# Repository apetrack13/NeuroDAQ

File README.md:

# NeuroDAQ
<p> The NeuroDAQ is a quality control device for transcranial electrical stimulation (tES) generation devices.
The aim is to improve the outcomes of tES studies by verifying the fidelity of stimulation generation from
tES devices. </p>
<h2>Setting Up the NeuroDAQ</h2>
<p> The NeuroDAQ requires a connection to a local network. </p>

<h3>Setup Wireless Connection</h3>

1.)	Check if micro USB power cable is connected to NeuroDAQ located on the side.

2.)	Remove micro SD card from NeuroDAQ located on the side. 

3.)	Insert micro SD card into adaptor SD card adaptor provided with kit.

4.)	Plug the SD Card adaptor into computer. A new volume should appear in your finder/ file explorer.

5.)	Open the new volume and navigate to the boot directory /Volumes/boot.

6.)	Create a file called wpa_supplicant.conf in this directory and save it.

7.)	Open the file and add the following details:                                                					network={												ssid=”YOUR_NETWORK_NAME”									psk=”YOUR_PASSWORD”									key_mgmt=WPA-PSK

8.)	Eject the SD card and plug it back into the NeuroDAQ.

<h2>Using the NeuroDAQ via Terminal</h2>
<h3>Establish SSH Connection to NeuroDAQ</h3>
<p>
The NeuroDAQ can be controlled via a ssh connection. Once a ssh connection is established, data acquisition can be iniated.
</p>
1.)	First, be sure the micro USB power cable is connected to the NeuroDAQ.

2.)	Open terminal in the applications folder of Mac OS computer.

3.)	Type ssh pi@NeuroDAQ.local and press enter.

4.)	If prompted to answer a yes or no question, type yes and press enter. If not, skip to step 4.

5.)	You will be prompted to enter a password to connect to the device. The password is “GIZMO629” (obviously no quotes).

6.)	You are now connected to the device’s terminal from which you can execute scripts.

<h3>Retrieve Data File</h3>
1.)	In the Mac OS terminal connected to the device, type and enter:					scp pi@NeuroDAQ.local:~/Desktop/DATA_FILE_NAME.csv ~/Desktop		

Replace DATA_FILE_NAME with what you named the data file during data acquisition. 

2.)	The data file will be transferred to the desktop of your Mac OS computer. You now can process this data file with the MATLAB script provided.

<h3>Process Data File with MATLAB</h3>
1.)	Locate the MATLAB script file named “Process_Signal.m”. This script is available at github.com/NeuroModQC-WSU-Design/NeuroDAQ/.

2.)	Place the data file in the same directory as this script.

3.)	Open the script with MATLAB and run.

4.)	You will be prompted to answer questions about the stimulation paradigm recorded. Please, refer to the stimulation paradigm parameters used to record the data file.

5.)	Statistical analysis and graphs of stimulation paradigm will be presented.

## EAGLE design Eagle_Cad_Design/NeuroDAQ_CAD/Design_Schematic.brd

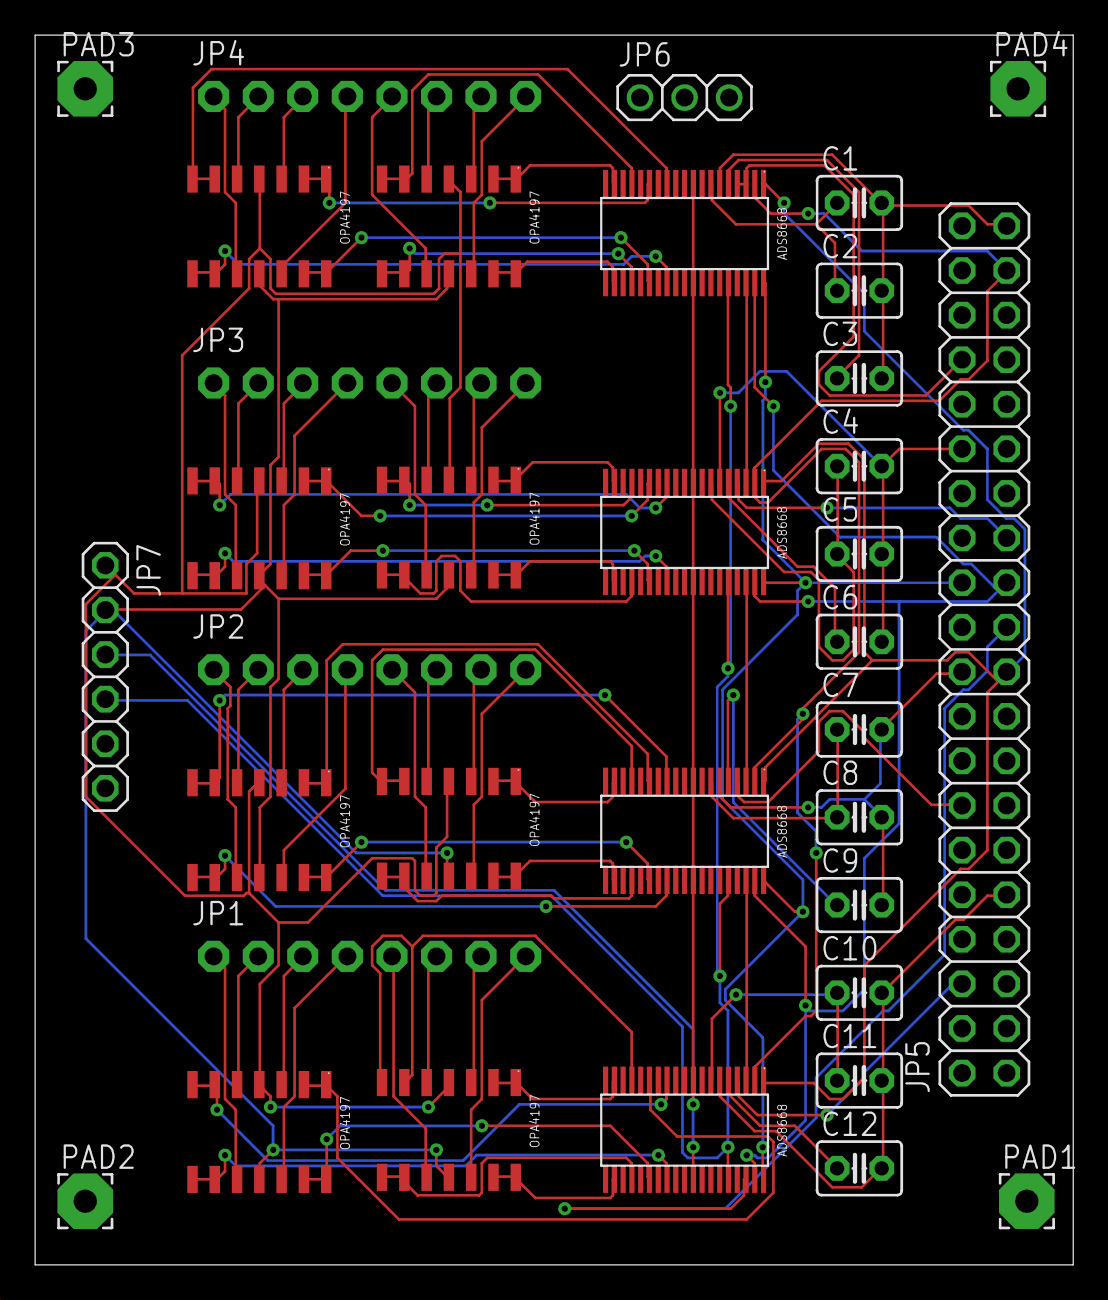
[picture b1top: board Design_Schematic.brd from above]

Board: 2 copper layers, 59.1 x 70.1 mm, 35 parts (0 on the bottom side), 93 nets.

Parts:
ADC1, ADC2, ADC3, ADC4: ADS8668
C1, C2, C3, C4, C5, C6, C7, C8, C9, C10, C11, C12: C025-030X050
JP1, JP2, JP3, JP4: 1X08-CLEANBIG
JP5: 2X20
JP6: 1X03
JP7: 1X06
PAD1, PAD2, PAD3, PAD4: 3,17/1,3
U$1, U$2, U$3, U$4, U$5, U$6, U$7, U$8: OPA4197

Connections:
+3.3V: ADC1.DVDD, ADC2.DVDD, ADC3.DVDD, ADC4.DVDD, JP7.4
+5V: ADC1.AVDD0, ADC1.AVDD1, ADC2.AVDD0, ADC2.AVDD1, ADC3.AVDD0, ADC3.AVDD1, ADC4.AVDD0, ADC4.AVDD1, JP7.3
+12V: JP7.1, U$1.V+, U$2.V+, U$3.V+, U$4.V+, U$5.V+, U$6.V+, U$7.V+, U$8.V+
-12V: JP7.2, U$1.V-, U$2.V-, U$3.V-, U$4.V-, U$5.V-, U$6.V-, U$7.V-, U$8.V-
CLK: ADC1.SCLK, ADC2.SCLK, ADC3.SCLK, ADC4.SCLK, JP5.23
COM: ADC1.AGND0, ADC1.AGND1, ADC1.AGND2, ADC1.AGND3, ADC1.AGND4, ADC1.AIN2_GND, ADC1.AIN6_GND, ADC1.AIN_0GND, ADC1.AIN_1GND, ADC1.AIN_3GND, ADC1.AIN_4GND, ADC1.AIN_5GND, ADC1.AIN_7GND, ADC1.ALARM, ADC1.AUX_GND, ADC1.AUX_IN, ADC1.DGND, ADC2.AGND0, ADC2.AGND1, ADC2.AGND2, ADC2.AGND3, ADC2.AGND4, ADC2.AIN2_GND, ADC2.AIN6_GND, ADC2.AIN_0GND, ADC2.AIN_1GND, ADC2.AIN_3GND, ADC2.AIN_4GND, ADC2.AIN_5GND, ADC2.AIN_7GND, ADC2.ALARM, ADC2.AUX_GND, ADC2.AUX_IN, ADC2.DGND, ADC3.AGND0, ADC3.AGND1, ADC3.AGND2, ADC3.AGND3, ADC3.AGND4, ADC3.AIN2_GND, ADC3.AIN6_GND, ADC3.AIN_0GND, ADC3.AIN_1GND, ADC3.AIN_3GND, ADC3.AIN_4GND, ADC3.AIN_5GND, ADC3.AIN_7GND, ADC3.ALARM, ADC3.AUX_GND, ADC3.AUX_IN, ADC3.DGND, ADC4.AGND0, ADC4.AGND1, ADC4.AGND2, ADC4.AGND3, ADC4.AGND4, ADC4.AIN2_GND, ADC4.AIN6_GND, ADC4.AIN_0GND, ADC4.AIN_1GND, ADC4.AIN_3GND, ADC4.AIN_4GND, ADC4.AIN_5GND, ADC4.AIN_7GND, ADC4.ALARM, ADC4.AUX_GND, ADC4.AUX_IN, ADC4.DGND, JP6.1, JP6.2, JP6.3, JP7.5, JP7.6, PAD1.1, PAD2.1, PAD3.1, PAD4.1
COM1: ADC4.REFGND, C1.2, C2.2, C3.2, JP5.39
COM2: ADC1.REFGND, C4.2, C5.2, C6.2, JP5.30
COM3: ADC2.REFGND, C7.2, C8.2, C9.2, JP5.20
COM4: ADC3.REFGND, C10.2, C11.2, C12.2, JP5.9
COM11: ADC4.DAISY, ADC4.REFSEL, JP5.34
COM22: ADC1.REFSEL, JP5.25
COM33: ADC2.REFSEL, JP5.14
COM44: ADC3.REFSEL, JP5.6
CS: ADC1.CS, ADC2.CS, ADC3.CS, ADC4.CS, JP5.24
DAISY2: ADC1.DAISY, ADC4.SDO
DAISY3: ADC1.SDO, ADC2.DAISY
DAISY4: ADC2.SDO, ADC3.DAISY
IN1: JP1.3, U$5.+INA
IN2: JP1.2, U$5.+INB
IN3: JP1.1, U$5.+INC
IN4: JP1.4, U$5.+IND
IN5: JP1.7, U$1.+INA
IN6: JP1.6, U$1.+INB
IN7: JP1.5, U$1.+INC
IN8: JP1.8, U$1.+IND
IN9: JP2.2, U$2.+INB
IN10: JP2.3, U$2.+INA
IN11: JP2.4, U$2.+IND
IN12: JP2.1, U$2.+INC
IN13: JP2.7, U$3.+INA
IN14: JP2.6, U$3.+INB
IN15: JP2.5, U$3.+INC
IN16: JP2.8, U$3.+IND
IN17: JP3.3, U$4.+INA
IN18: JP3.2, U$4.+INB
IN19: JP3.1, U$4.+INC
IN20: JP3.4, U$4.+IND
IN21: JP3.7, U$6.+INA
IN22: JP3.6, U$6.+INB
IN23: JP3.5, U$6.+INC
IN24: JP3.8, U$6.+IND
IN25: JP4.2, U$7.+INB
IN26: JP4.3, U$7.+INA
IN27: JP4.4, U$7.+IND
IN28: JP4.1, U$7.+INC
IN29: JP4.7, U$8.+INA
IN30: JP4.6, U$8.+INB
IN31: JP4.5, U$8.+INC
IN32: JP4.8, U$8.+IND
MISO: ADC3.SDO, JP5.21
MOSI: ADC1.SDI, ADC2.SDI, ADC3.SDI, ADC4.SDI, JP5.19
OUT1: ADC3.AIN_7P, U$5.-INA, U$5.OUTA
OUT2: ADC3.AIN_6P, U$5.-INB, U$5.OUTB
OUT3: ADC3.AIN_5P, U$5.-INC, U$5.OUTC
OUT4: ADC3.AIN_4P, U$5.-IND, U$5.OUTD
OUT5: ADC3.AIN_1P, U$1.-INA, U$1.OUTA
OUT6: ADC3.AIN_0P, U$1.-INB, U$1.OUTB
OUT7: ADC3.AIN_3P, U$1.-INC, U$1.OUTC
OUT8: ADC3.AIN_2P, U$1.-IND, U$1.OUTD
OUT9: ADC2.AIN_6P, U$2.-INB, U$2.OUTB
OUT10: ADC2.AIN_7P, U$2.-INA, U$2.OUTA
OUT11: ADC2.AIN_4P, U$2.-IND, U$2.OUTD
OUT12: ADC2.AIN_5P, U$2.-INC, U$2.OUTC
OUT13: ADC2.AIN_1P, U$3.-INA, U$3.OUTA
OUT14: ADC2.AIN_0P, U$3.-INB, U$3.OUTB
OUT15: ADC2.AIN_3P, U$3.-INC, U$3.OUTC
OUT16: ADC2.AIN_2P, U$3.-IND, U$3.OUTD
OUT17: ADC1.AIN_7P, U$4.-INA, U$4.OUTA
OUT18: ADC1.AIN_6P, U$4.-INB, U$4.OUTB
OUT19: ADC1.AIN_5P, U$4.-INC, U$4.OUTC
OUT20: ADC1.AIN_4P, U$4.-IND, U$4.OUTD
OUT21: ADC1.AIN_1P, U$6.-INA, U$6.OUTA
OUT22: ADC1.AIN_0P, U$6.-INB, U$6.OUTB
OUT23: ADC1.AIN_3P, U$6.-INC, U$6.OUTC
OUT24: ADC1.AIN_2P, U$6.-IND, U$6.OUTD
OUT25: ADC4.AIN_6P, U$7.-INB, U$7.OUTB
OUT26: ADC4.AIN_7P, U$7.-INA, U$7.OUTA
OUT27: ADC4.AIN_4P, U$7.-IND, U$7.OUTD
OUT28: ADC4.AIN_5P, U$7.-INC, U$7.OUTC
OUT29: ADC4.AIN_1P, U$8.-INA, U$8.OUTA
OUT30: ADC4.AIN_0P, U$8.-INB, U$8.OUTB
OUT31: ADC4.AIN_3P, U$8.-INC, U$8.OUTC
OUT32: ADC4.AIN_2P, U$8.-IND, U$8.OUTD
REFCAP1: ADC4.REFCAP, C1.1, C2.1
REFCAP2: ADC1.REFCAP, C4.1, C5.1
REFCAP3: ADC2.REFCAP, C7.1, C8.1
REFCAP4: ADC3.REFCAP, C10.1, C11.1
REFIO1: ADC4.REFIO, C3.1
REFIO2: ADC1.REFIO, C6.1
REFIO3: ADC2.REFIO, C9.1
REFIO4: ADC3.REFIO, C12.1
RST: ADC1.RST/PD, ADC2.RST/PD, ADC3.RST/PD, ADC4.RST/PD, JP5.37

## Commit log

2018-04-16 Initial Commit - Added Base Files for NeuroDAQ
2018-04-16 Added Eagle CAD design of NeuroDAQ.
2018-04-16 Fixed directory.
2018-04-16 README.md
    Created README for introduction to project and how to use the NeuroDAQ.
2018-04-21 Added case CAD drawing.
2018-04-21 Fixed clock rate in libraries and file writing.
